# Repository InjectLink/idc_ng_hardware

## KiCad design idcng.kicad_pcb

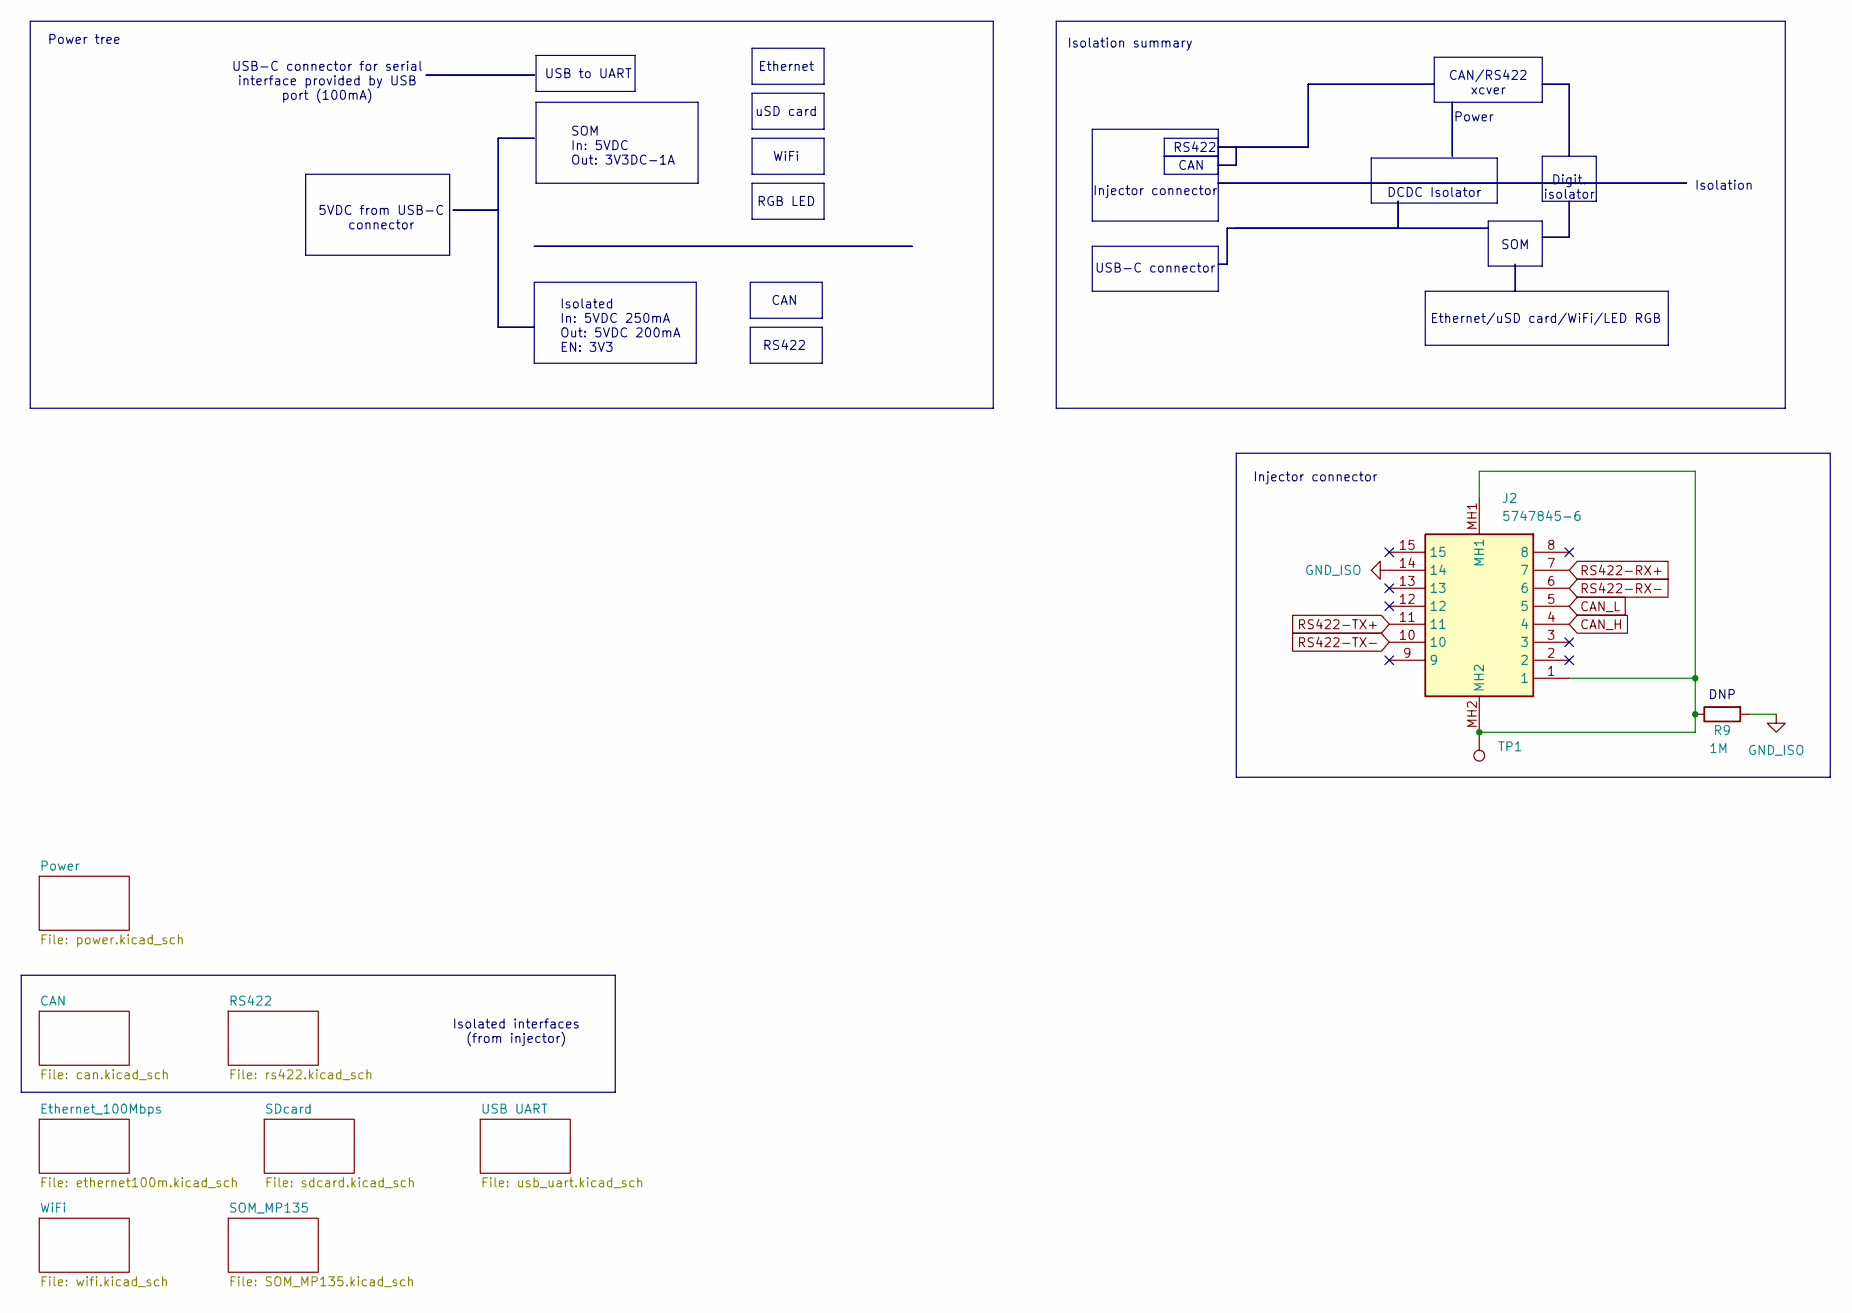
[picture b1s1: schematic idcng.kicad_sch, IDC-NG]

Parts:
J2: 5747845-6; 57478456; Mouser Part Number 571-5747845-6
R9: 1M; R_1206_3216Metric
TP1: TestPoint; TestPoint_Pad_D1.0mm

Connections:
CAN_H: J2.4; also elsewhere on the board
CAN_L: J2.5; also elsewhere on the board
GND_ISO: J2.14, R9.2; also elsewhere on the board
unnamed: J2.1, J2.MH1, J2.MH2, R9.1, TP1.1
RS422-RX+: J2.7; also elsewhere on the board
RS422-RX-: J2.6; also elsewhere on the board
RS422-TX+: J2.11; also elsewhere on the board
RS422-TX-: J2.10; also elsewhere on the board

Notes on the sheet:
SOM In: 5VDC Out: 3V3DC-1A
WiFi
DCDC Isolator
5VDC from USB-C connector
SOM
Isolated In: 5VDC 250mA Out: 5VDC 200mA EN: 3V3
Injector connector
Ethernet/uSD card/WiFi/LED RGB
Isolated interfaces (from injector)
CAN/RS422 xcver
CAN
Power
RS422
Digit. isolator
uSD card
RGB LED
USB-C connector for serial interface provided by USB port (100mA)
USB to UART
Isolation summary
USB-C connector
Ethernet
Power tree
Isolation
DNP

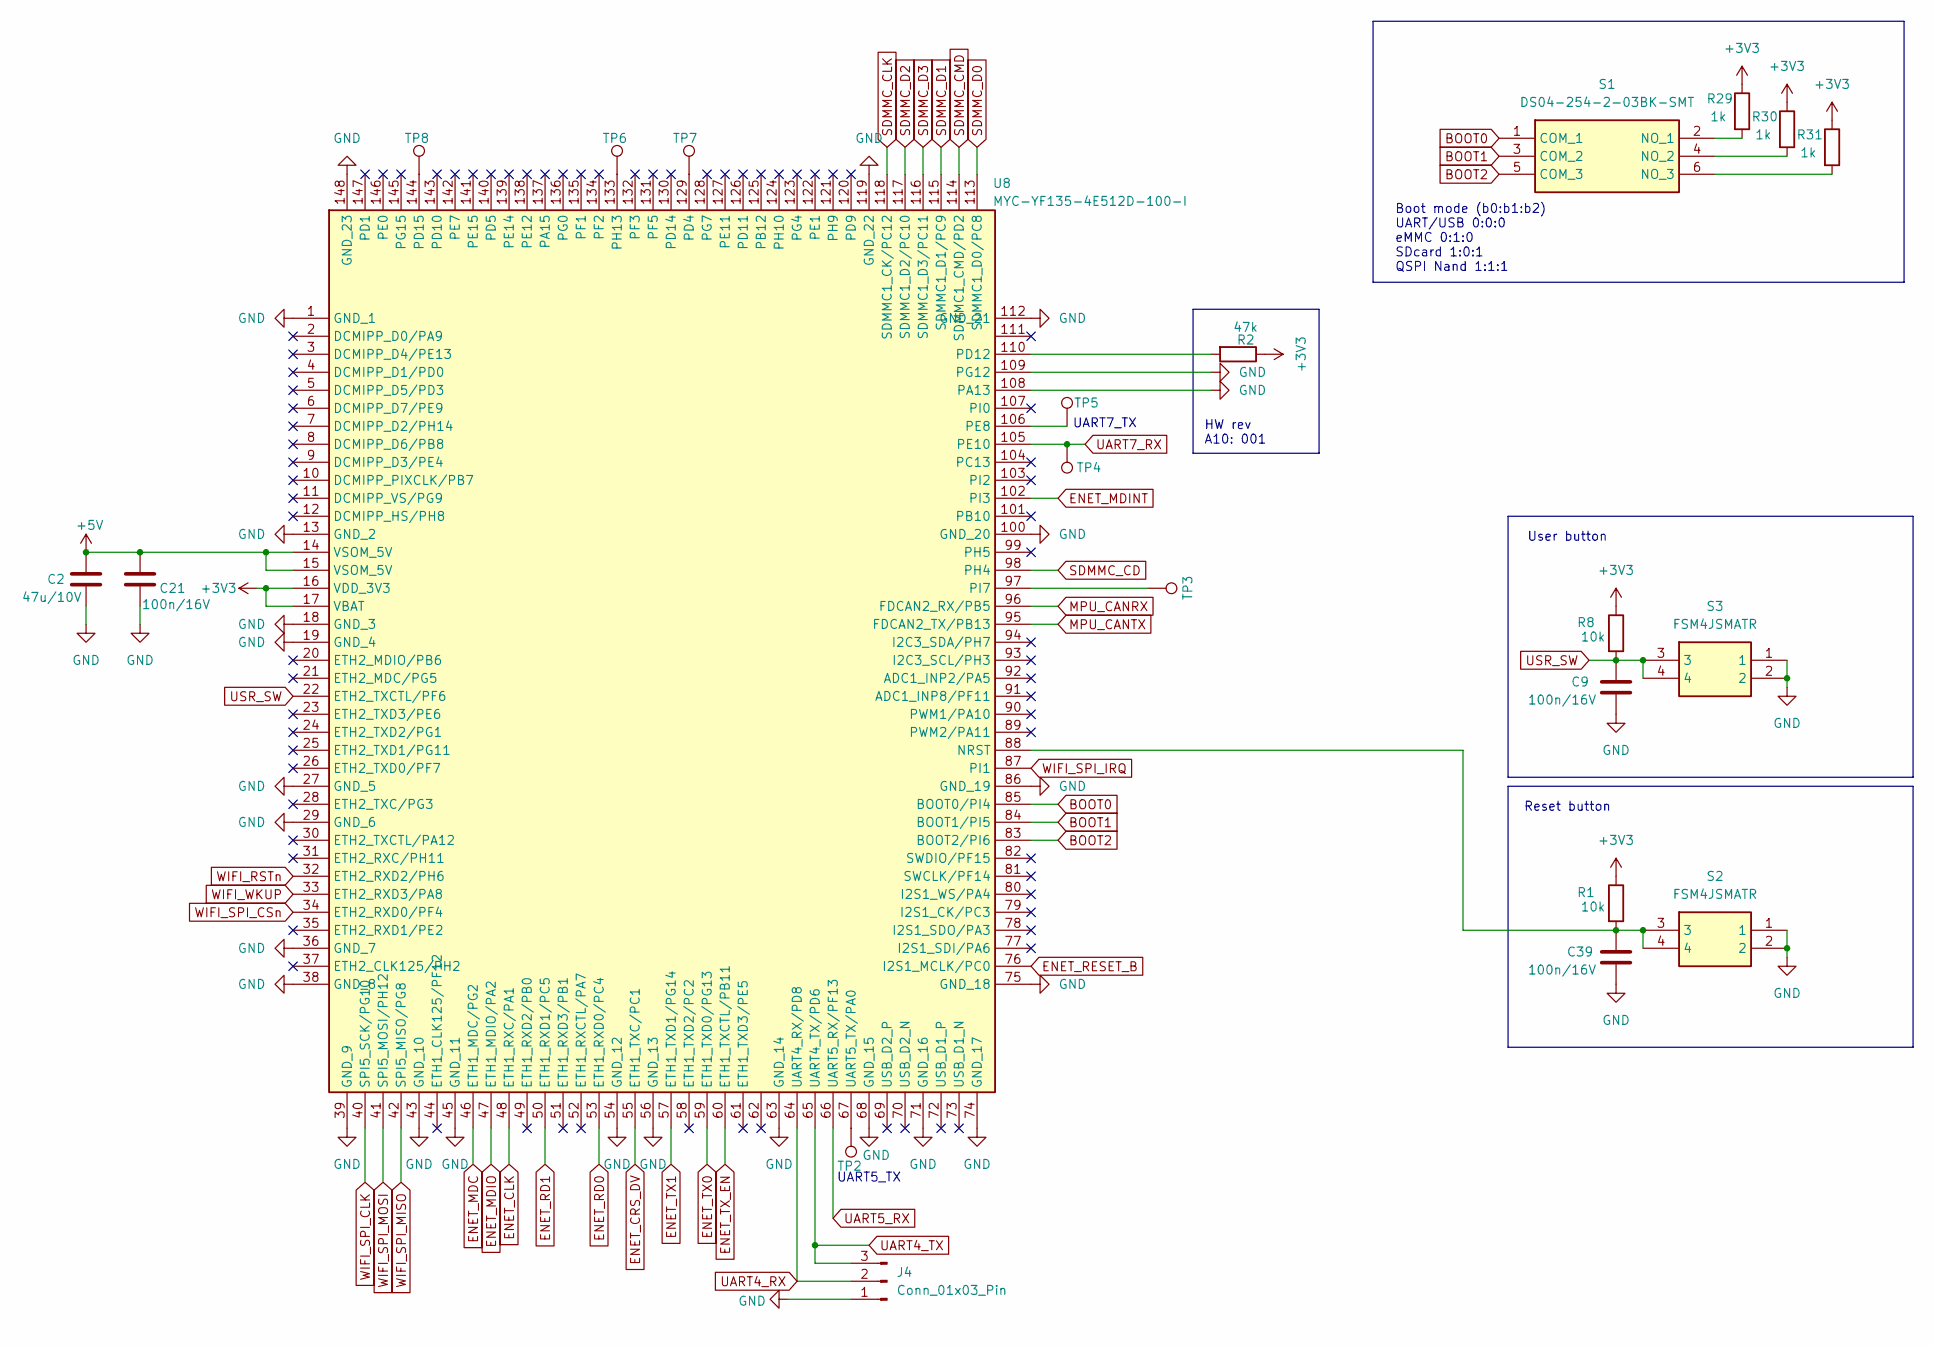
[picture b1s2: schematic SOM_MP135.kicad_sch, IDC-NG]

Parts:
C2: 47u/10V; C_1210_3225Metric
C9, C21, C39: 100n/16V; C_0201_0603Metric
J4: Conn_01x03_Pin; PinHeader_1x03_P1.00mm_Vertical
R1, R8: 10k; R_0201_0603Metric
R2: 47k; R_0201_0603Metric
R29, R30, R31: 1k; R_0201_0603Metric
S1: DS04-254-2-03BK-SMT; DS04254203BKSMT; Mouser Part Number 490-DS04254203BK-SMT
S2, S3: FSM4JSMATR; Mouser Part Number 506-FSM4JSMATR
TP2, TP3, TP4, TP5, TP6, TP7, TP8: TestPoint; TestPoint_Pad_D1.0mm
U8: MYC-YF135-4E512D-100-I; MYCYA151C256N256D65CT

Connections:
+3V3: R1.1, R2.1, R8.1, R29.1, R30.1, R31.1, U8.16 (VDD_3V3), U8.17 (VBAT); also elsewhere on the board
+5V: C2.1, C21.1, U8.14 (VSOM_5V), U8.15 (VSOM_5V); also elsewhere on the board
BOOT0: S1.1 (COM_1), U8.85 (BOOT0/PI4)
BOOT1: S1.3 (COM_2), U8.84 (BOOT1/PI5)
BOOT2: S1.5 (COM_3), U8.83 (BOOT2/PI6)
ENET_CLK: U8.48 (ETH1_RXC/PA1); also elsewhere on the board
ENET_CRS_DV: U8.55 (ETH1_TXC/PC1); also elsewhere on the board
ENET_MDC: U8.46 (ETH1_MDC/PG2); also elsewhere on the board
ENET_MDINT: U8.102 (PI3); also elsewhere on the board
ENET_MDIO: U8.47 (ETH1_MDIO/PA2); also elsewhere on the board
ENET_RD0: U8.53 (ETH1_RXD0/PC4); also elsewhere on the board
ENET_RD1: U8.50 (ETH1_RXD1/PC5); also elsewhere on the board
ENET_RESET_B: U8.76 (I2S1_MCLK/PC0); also elsewhere on the board
ENET_TX0: U8.59 (ETH1_TXD0/PG13); also elsewhere on the board
ENET_TX1: U8.57 (ETH1_TXD1/PG14); also elsewhere on the board
ENET_TX_EN: U8.60 (ETH1_TXCTL/PB11); also elsewhere on the board
GND: C2.2, C9.2, C21.2, C39.2, J4.1, S2.1, S2.2, S3.1, S3.2, U8.1 (GND_1), U8.13 (GND_2), U8.18 (GND_3), U8.19 (GND_4), U8.27 (GND_5), U8.29 (GND_6), U8.36 (GND_7), U8.38 (GND_8), U8.39 (GND_9), U8.43 (GND_10), U8.45 (GND_11), U8.54 (GND_12), U8.56 (GND_13), U8.63 (GND_14), U8.68 (GND_15), U8.71 (GND_16), U8.74 (GND_17), U8.75 (GND_18), U8.86 (GND_19), U8.100 (GND_20), U8.108 (PA13), U8.109 (PG12), U8.112 (GND_21), U8.119 (GND_22), U8.148 (GND_23); also elsewhere on the board
MPU_CANRX: U8.96 (FDCAN2_RX/PB5); also elsewhere on the board
MPU_CANTX: U8.95 (FDCAN2_TX/PB13); also elsewhere on the board
unnamed: R29.2, S1.2 (NO_1)
unnamed: R30.2, S1.4 (NO_2)
unnamed: R31.2, S1.6 (NO_3)
unnamed: C39.1, R1.2, S2.3, S2.4, U8.88 (NRST)
unnamed: TP7.1, U8.129 (PD4)
unnamed: R2.2, U8.110 (PD12)
unnamed: TP8.1, U8.144 (PD15)
unnamed: TP5.1, U8.106 (PE8)
unnamed: TP6.1, U8.133 (PH13)
unnamed: TP3.1, U8.97 (PI7)
unnamed: TP2.1, U8.67 (UART5_TX/PA0)
SDMMC_CD: U8.98 (PH4); also elsewhere on the board
SDMMC_CLK: U8.118 (SDMMC1_CK/PC12); also elsewhere on the board
SDMMC_CMD: U8.114 (SDMMC1_CMD/PD2); also elsewhere on the board
SDMMC_D0: U8.113 (SDMMC1_D0/PC8); also elsewhere on the board
SDMMC_D1: U8.115 (SDMMC1_D1/PC9); also elsewhere on the board
SDMMC_D2: U8.117 (SDMMC1_D2/PC10); also elsewhere on the board
SDMMC_D3: U8.116 (SDMMC1_D3/PC11); also elsewhere on the board
UART4_RX: J4.2, U8.64 (UART4_RX/PD8); also elsewhere on the board
UART4_TX: J4.3, U8.65 (UART4_TX/PD6); also elsewhere on the board
UART5_RX: U8.66 (UART5_RX/PF13); also elsewhere on the board
UART7_RX: TP4.1, U8.105 (PE10); also elsewhere on the board
USR_SW: C9.1, R8.2, S3.3, S3.4, U8.22 (ETH2_TXCTL/PF6)
WIFI_RSTn: U8.32 (ETH2_RXD2/PH6); also elsewhere on the board
WIFI_SPI_CLK: U8.40 (SPI5_SCK/PG10); also elsewhere on the board
WIFI_SPI_CSn: U8.34 (ETH2_RXD0/PF4); also elsewhere on the board
WIFI_SPI_IRQ: U8.87 (PI1); also elsewhere on the board
WIFI_SPI_MISO: U8.42 (SPI5_MISO/PG8); also elsewhere on the board
WIFI_SPI_MOSI: U8.41 (SPI5_MOSI/PH12); also elsewhere on the board
WIFI_WKUP: U8.33 (ETH2_RXD3/PA8); also elsewhere on the board

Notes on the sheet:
HW rev A10: 001
UART5_TX
Reset button
Boot mode (b0:b1:b2) UART/USB 0:0:0 eMMC 0:1:0 SDcard 1:0:1 QSPI Nand 1:1:1
UART7_TX
User button

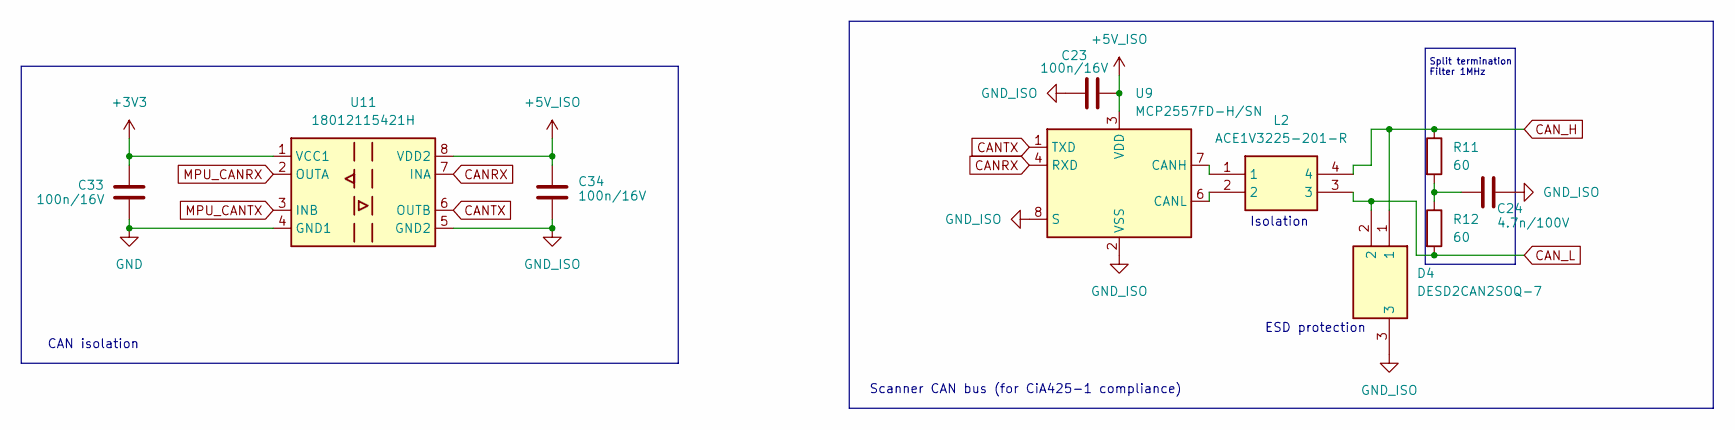
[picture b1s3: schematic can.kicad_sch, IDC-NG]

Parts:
C23, C33, C34: 100n/16V; C_0201_0603Metric
C24: 4.7n/100V; C_0603_1608Metric
D4: DESD2CAN2SOQ-7; SOT96P240X110-3N; Mouser Part Number 621-DESD2CAN2SOQ-7
L2: ACE1V3225-201-R; ACE1V3225201R; Mouser Part Number 504-ACE1V3225-201-R
R11, R12: 60; R_0201_0603Metric
U9: MCP2557FD-H/SN; SOIC-8_3.9x4.9mm_P1.27mm
U11: 18012115421H; SOIC-8_7.5x5.85mm_P1.27mm

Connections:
+3V3: C33.1, U11.1 (VCC1); also elsewhere on the board
+5V_ISO: C23.2, C34.1, U9.3 (VDD), U11.8 (VDD2); also elsewhere on the board
CANRX: U9.4 (RXD), U11.7 (INA)
CANTX: U9.1 (TXD), U11.6 (OUTB)
CAN_H: D4.1, L2.4, R11.1; also elsewhere on the board
CAN_L: D4.2, L2.3, R12.2; also elsewhere on the board
GND: C33.2, U11.4 (GND1); also elsewhere on the board
GND_ISO: C23.1, C24.1, C34.2, D4.3, U9.2 (VSS), U9.8 (S), U11.5 (GND2); also elsewhere on the board
MPU_CANRX: U11.2 (OUTA); also elsewhere on the board
MPU_CANTX: U11.3 (INB); also elsewhere on the board
unnamed: C24.2, R11.2, R12.1
unnamed: L2.1, U9.7 (CANH)
unnamed: L2.2, U9.6 (CANL)

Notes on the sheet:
ESD protection
Scanner CAN bus (for CiA425-1 compliance)
Split termination Filter 1MHz
Isolation
CAN isolation

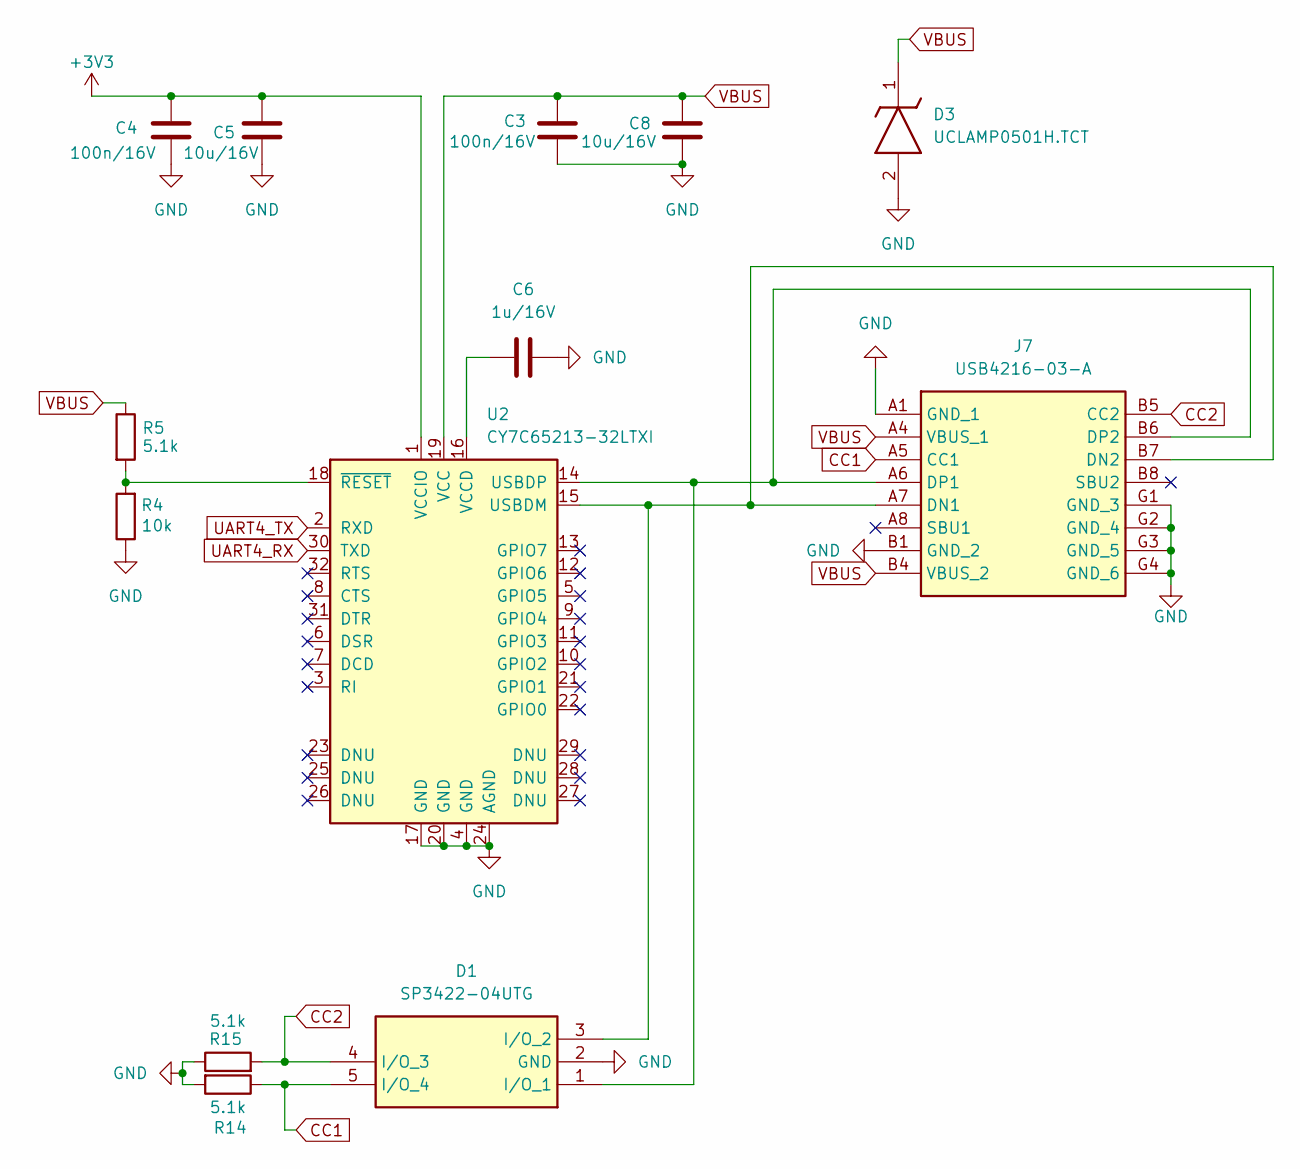
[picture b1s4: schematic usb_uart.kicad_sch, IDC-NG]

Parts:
C3, C4: 100n/16V; C_0201_0603Metric
C5, C8: 10u/16V; C_0805_2012Metric
C6: 1u/16V; C_0603_1608Metric
D1: SP3422-04UTG; SP342204UTG; Mouser Part Number 576-SP3422-04UTG
D3: UCLAMP0501H.TCT; SODFL1608X70N; Mouser Part Number 947-UCLAMP0501H.TCT
J7: USB4216-03-A; USB421603A; Mouser Part Number 640-USB4216-03-A
R4: 10k; R_0201_0603Metric
R5, R14, R15: 5.1k; R_0201_0603Metric
U2: CY7C65213-32LTXI; QFN-32-1EP_5x5mm_P0.5mm_EP3.45x3.45mm

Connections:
+3V3: C4.1, C5.1, U2.1 (VCCIO); also elsewhere on the board
CC1: D1.5 (I/O_4), J7.A5 (CC1), R14.1
CC2: D1.4 (I/O_3), J7.B5 (CC2), R15.2
GND: C3.2, C4.2, C5.2, C6.1, C8.2, D1.2 (GND), D3.2 (A), J7.A1 (GND_1), J7.B1 (GND_2), J7.G1 (GND_3), J7.G2 (GND_4), J7.G3 (GND_5), J7.G4 (GND_6), R4.1, R14.2, R15.1, U2.4 (GND), U2.17 (GND), U2.20 (GND), U2.24 (AGND); also elsewhere on the board
unnamed: D1.1 (I/O_1), J7.A6 (DP1), J7.B6 (DP2), U2.14 (USBDP)
unnamed: D1.3 (I/O_2), J7.A7 (DN1), J7.B7 (DN2), U2.15 (USBDM)
unnamed: C6.2, U2.16 (VCCD)
unnamed: R4.2, R5.2, U2.18 (~RESET)
UART4_RX: U2.30 (TXD); also elsewhere on the board
UART4_TX: U2.2 (RXD); also elsewhere on the board
VBUS: C3.1, C8.1, D3.1 (K), J7.A4 (VBUS_1), J7.B4 (VBUS_2), R5.1, U2.19 (VCC)

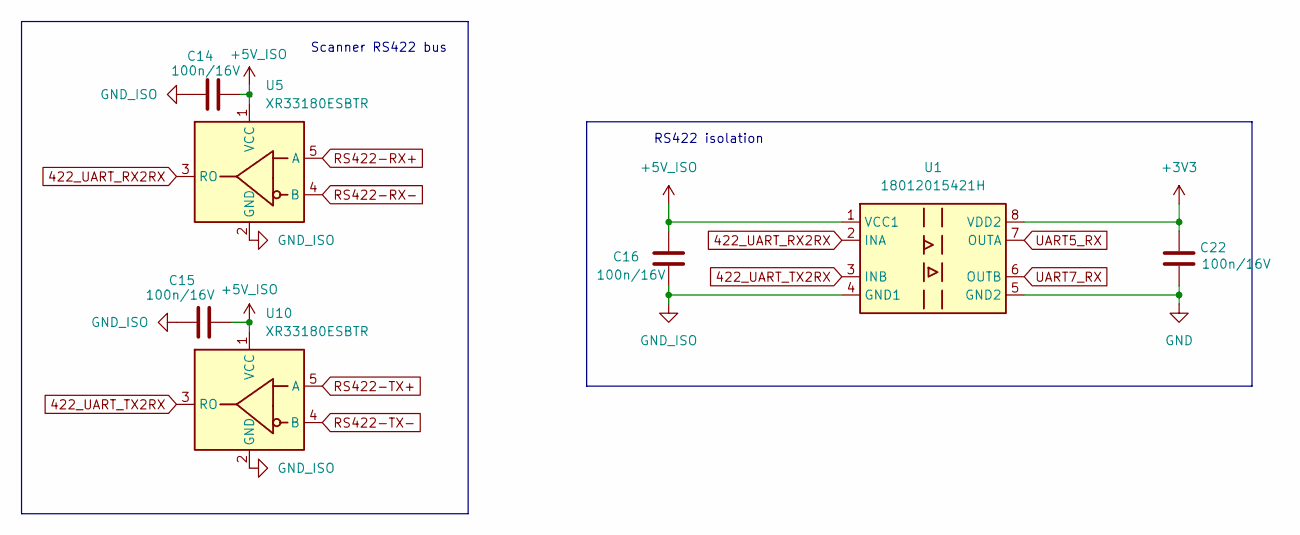
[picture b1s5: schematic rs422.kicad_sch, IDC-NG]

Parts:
C14, C15, C16, C22: 100n/16V; C_0201_0603Metric
U1: 18012015421H; SOIC-8_7.5x5.85mm_P1.27mm
U5, U10: XR33180ESBTR; TSOT-23-5

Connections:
422_UART_RX2RX: U1.2 (INA), U5.3 (RO)
422_UART_TX2RX: U1.3 (INB), U10.3 (RO)
+3V3: C22.1, U1.8 (VDD2); also elsewhere on the board
+5V_ISO: C14.1, C15.1, C16.1, U1.1 (VCC1), U5.1 (VCC), U10.1 (VCC); also elsewhere on the board
GND: C22.2, U1.5 (GND2); also elsewhere on the board
GND_ISO: C14.2, C15.2, C16.2, U1.4 (GND1), U5.2 (GND), U10.2 (GND); also elsewhere on the board
RS422-RX+: U5.5 (A); also elsewhere on the board
RS422-RX-: U5.4 (B); also elsewhere on the board
RS422-TX+: U10.5 (A); also elsewhere on the board
RS422-TX-: U10.4 (B); also elsewhere on the board
UART5_RX: U1.7 (OUTA); also elsewhere on the board
UART7_RX: U1.6 (OUTB); also elsewhere on the board

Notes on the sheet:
RS422 isolation
Scanner RS422 bus

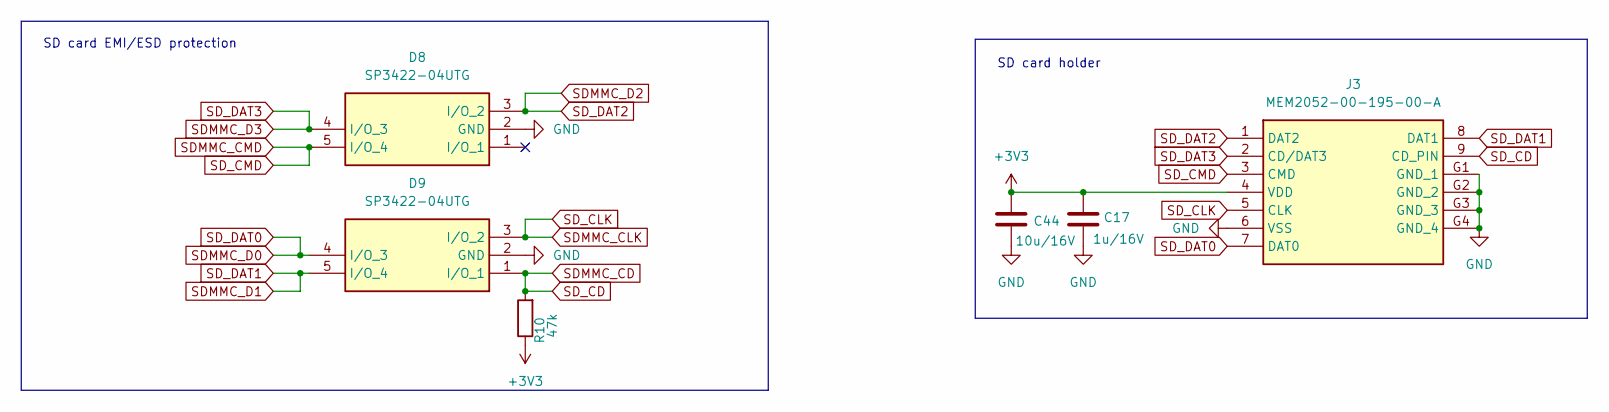
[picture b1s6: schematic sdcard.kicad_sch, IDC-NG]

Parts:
C17: 1u/16V; C_0603_1608Metric
C44: 10u/16V; C_0805_2012Metric
D8, D9: SP3422-04UTG; SP342204UTG; Mouser Part Number 576-SP3422-04UTG
J3: MEM2052-00-195-00-A; MEM20520019500A; Mouser Part Number 640-MEM20520019500A
R10: 47k; R_0201_0603Metric

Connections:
+3V3: C17.1, C44.1, J3.4 (VDD), R10.1; also elsewhere on the board
GND: C17.2, C44.2, D8.2 (GND), D9.2 (GND), J3.6 (VSS), J3.G1 (GND_1), J3.G2 (GND_2), J3.G3 (GND_3), J3.G4 (GND_4); also elsewhere on the board
SDMMC_CD: D9.1 (I/O_1), J3.9 (CD_PIN), R10.2; also elsewhere on the board
SDMMC_CLK: D9.3 (I/O_2), J3.5 (CLK); also elsewhere on the board
SDMMC_CMD: D8.5 (I/O_4), J3.3 (CMD); also elsewhere on the board
SDMMC_D0: D9.4 (I/O_3), J3.7 (DAT0); also elsewhere on the board
SDMMC_D1: D9.5 (I/O_4), J3.8 (DAT1); also elsewhere on the board
SDMMC_D2: D8.3 (I/O_2), J3.1 (DAT2); also elsewhere on the board
SDMMC_D3: D8.4 (I/O_3), J3.2 (CD/DAT3); also elsewhere on the board

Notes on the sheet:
SD card EMI/ESD protection
SD card holder

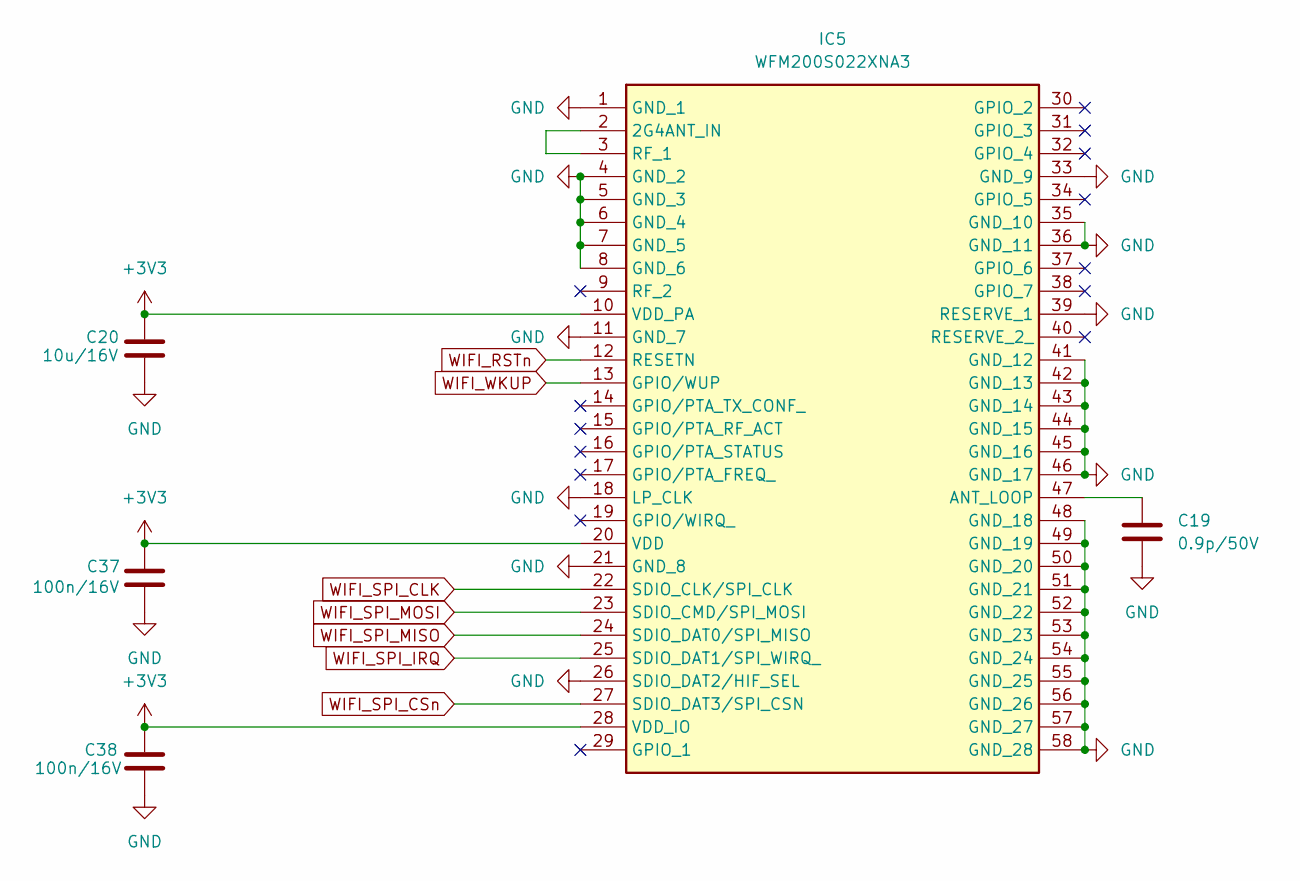
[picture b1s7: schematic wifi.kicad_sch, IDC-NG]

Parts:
C19: 0.9p/50V; C_0201_0603Metric
C20: 10u/16V; C_0805_2012Metric
C37, C38: 100n/16V; C_0201_0603Metric
IC5: WFM200S022XNA3; Mouser Part Number 634-WFM200S022XNA3

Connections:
+3V3: C20.1, C37.1, C38.1, IC5.10 (VDD_PA), IC5.20 (VDD), IC5.28 (VDD_IO); also elsewhere on the board
GND: C19.2, C20.2, C37.2, C38.2, IC5.1 (GND_1), IC5.4 (GND_2), IC5.5 (GND_3), IC5.6 (GND_4), IC5.7 (GND_5), IC5.8 (GND_6), IC5.11 (GND_7), IC5.18 (LP_CLK), IC5.21 (GND_8), IC5.26 (SDIO_DAT2/HIF_SEL), IC5.33 (GND_9), IC5.35 (GND_10), IC5.36 (GND_11), IC5.39 (RESERVE_1), IC5.41 (GND_12), IC5.42 (GND_13), IC5.43 (GND_14), IC5.44 (GND_15), IC5.45 (GND_16), IC5.46 (GND_17), IC5.48 (GND_18), IC5.49 (GND_19), IC5.50 (GND_20), IC5.51 (GND_21), IC5.52 (GND_22), IC5.53 (GND_23), IC5.54 (GND_24), IC5.55 (GND_25), IC5.56 (GND_26), IC5.57 (GND_27), IC5.58 (GND_28); also elsewhere on the board
unnamed: IC5.2 (2G4ANT_IN), IC5.3 (RF_1)
unnamed: C19.1, IC5.47 (ANT_LOOP)
WIFI_RSTn: IC5.12 (RESETN); also elsewhere on the board
WIFI_SPI_CLK: IC5.22 (SDIO_CLK/SPI_CLK); also elsewhere on the board
WIFI_SPI_CSn: IC5.27 (SDIO_DAT3/SPI_CSN); also elsewhere on the board
WIFI_SPI_IRQ: IC5.25 (SDIO_DAT1/SPI_WIRQ_); also elsewhere on the board
WIFI_SPI_MISO: IC5.24 (SDIO_DAT0/SPI_MISO); also elsewhere on the board
WIFI_SPI_MOSI: IC5.23 (SDIO_CMD/SPI_MOSI); also elsewhere on the board
WIFI_WKUP: IC5.13 (GPIO/WUP); also elsewhere on the board

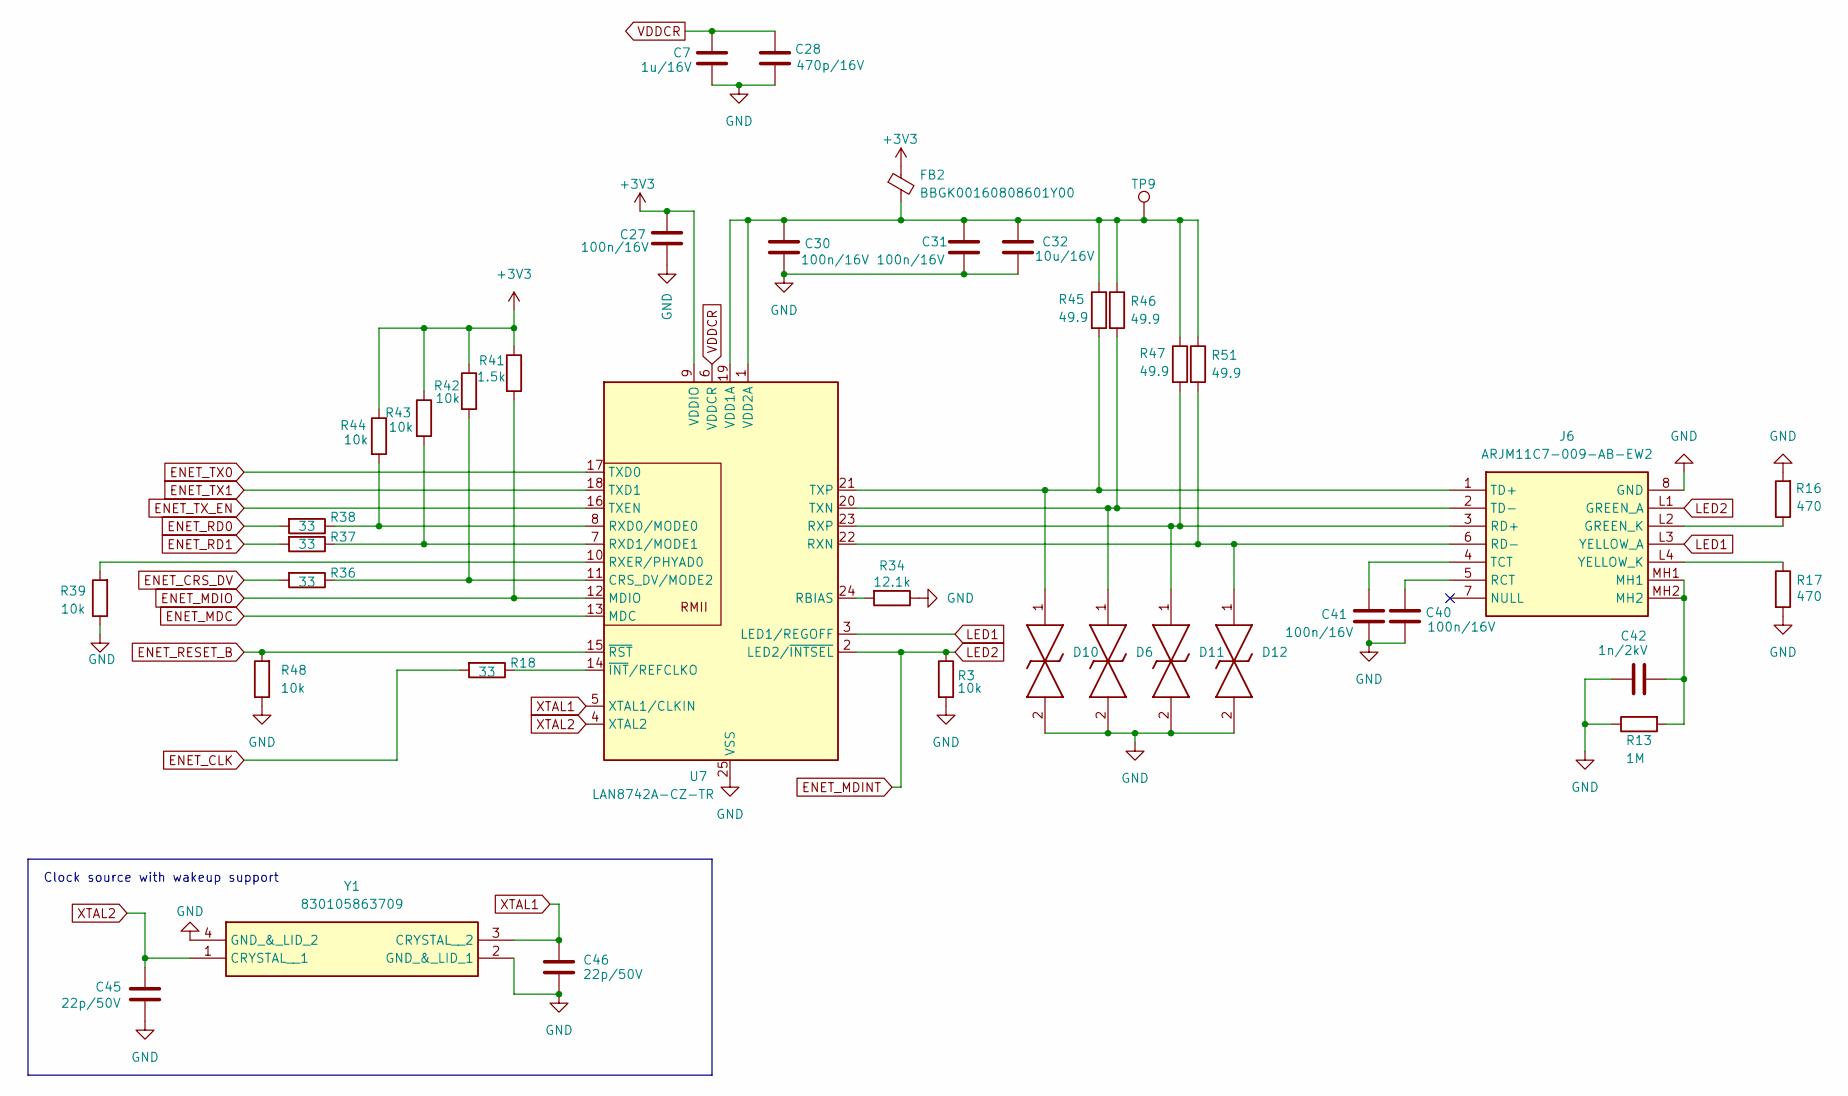
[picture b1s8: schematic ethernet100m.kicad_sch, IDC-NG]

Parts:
C7: 1u/16V; C_0603_1608Metric
C27, C30, C31, C40, C41: 100n/16V; C_0201_0603Metric
C28: 470p/16V; C_0402_1005Metric
C32: 10u/16V; C_0805_2012Metric
C42: 1n/2kV; C_1206_3216Metric
C45, C46: 22p/50V; C_0201_0603Metric
D6, D10, D11, D12: AQ3130-01ETG; AQ313001ETG; Mouser Part Number 576-AQ3130-01ETG
FB2: BBGK00160808601Y00; L_0603_1608Metric
J6: ARJM11C7-009-AB-EW2; ARJM11C7009ABEW2; Mouser Part Number 815-RJM11C7009ABEW2
R3, R39, R42, R43, R44, R48: 10k; R_0201_0603Metric
R13: 1M; R_1206_3216Metric
R16, R17: 470; L_0402_1005Metric
R18, R36, R37, R38: 33; R_0201_0603Metric
R34: 12.1k; R_0201_0603Metric
R41: 1.5k; R_0402_1005Metric; Part AC0402FR-7W1K5L
R45, R46, R47, R51: 49.9; R_0201_0603Metric
TP9: TestPoint; TestPoint_Pad_D1.0mm
U7: LAN8742A-CZ-TR; VQFN-24-1EP_4x4mm_P0.5mm_EP2.5x2.5mm_ThermalVias
Y1: 830105863709; Mouser Part Number 710-830105863709

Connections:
+3V3: C27.1, FB2.1, R41.1, R42.1, R43.1, R44.1, U7.9 (VDDIO); also elsewhere on the board
ENET_CLK: R18.2; also elsewhere on the board
ENET_CRS_DV: R36.2; also elsewhere on the board
ENET_MDC: U7.13 (MDC); also elsewhere on the board
ENET_MDINT: J6.L1 (GREEN_A), R3.1, U7.2 (LED2/~INTSEL); also elsewhere on the board
ENET_MDIO: R41.2, U7.12 (MDIO); also elsewhere on the board
ENET_RD0: R38.2; also elsewhere on the board
ENET_RD1: R37.2; also elsewhere on the board
ENET_RESET_B: R48.2, U7.15 (~RST); also elsewhere on the board
ENET_TX0: U7.17 (TXD0); also elsewhere on the board
ENET_TX1: U7.18 (TXD1); also elsewhere on the board
ENET_TX_EN: U7.16 (TXEN); also elsewhere on the board
GND: C7.2, C27.2, C28.2, C30.1, C31.1, C32.1, C40.1, C41.1, C42.1, C45.2, C46.2, D6.2, D10.2, D11.2, D12.2, J6.8 (GND), R3.2, R13.1, R16.2, R17.2, R34.1, R39.1, R48.1, U7.25 (VSS), Y1.2 (GND_&_LID_1), Y1.4 (GND_&_LID_2); also elsewhere on the board
LED1: J6.L3 (YELLOW_A), U7.3 (LED1/REGOFF)
unnamed: C42.2, J6.MH1, J6.MH2, R13.2
unnamed: J6.L2 (GREEN_K), R16.1
unnamed: C40.2, J6.5 (RCT)
unnamed: D11.1, J6.3 (RD+), R47.2, U7.23 (RXP)
unnamed: D12.1, J6.6 (RD-), R51.2, U7.22 (RXN)
unnamed: C41.2, J6.4 (TCT)
unnamed: D10.1, J6.1 (TD+), R45.2, U7.21 (TXP)
unnamed: D6.1, J6.2 (TD-), R46.2, U7.20 (TXN)
unnamed: J6.L4 (YELLOW_K), R17.1
unnamed: R36.1, R42.2, U7.11 (CRS_DV/MODE2)
unnamed: R34.2, U7.24 (RBIAS)
unnamed: R38.1, R44.2, U7.8 (RXD0/MODE0)
unnamed: R37.1, R43.2, U7.7 (RXD1/MODE1)
unnamed: R39.2, U7.10 (RXER/PHYAD0)
unnamed: C30.2, C31.2, C32.2, FB2.2, R45.1, R46.1, R47.1, R51.1, TP9.1, U7.1 (VDD2A), U7.19 (VDD1A)
unnamed 59: R18.1, U7.14 (~INT/REFCLKO); also elsewhere on the board
VDDCR: C7.1, C28.1, U7.6 (VDDCR)
XTAL1: C46.1, U7.5 (XTAL1/CLKIN), Y1.3 (CRYSTAL__2)
XTAL2: C45.1, U7.4 (XTAL2), Y1.1 (CRYSTAL__1)

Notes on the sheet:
Clock source with wakeup support

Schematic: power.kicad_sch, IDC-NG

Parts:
C1, C35: 100n/16V; C_0201_0603Metric
C10: 1nF/300VAC; VY2102M29Y5US6TV7; Mouser Part Number 72-VY2102M29Y5US6TV7
C36: 10u/16V; C_0805_2012Metric
C43: 22u/16V; C_0603_1608Metric
D2: UCLAMP0501H.TCT; SODFL1608X70N; Mouser Part Number 947-UCLAMP0501H.TCT
D7: SP3422-04UTG; SP342204UTG; Mouser Part Number 576-SP3422-04UTG
F1: SF-0603F250-2; Fuse_0603_1608Metric
IC1: MIE1W0505BGLVH-3R-P; MIE1W0505BGLVH3RP; Mouser Part Number 946-MIE1W0505BGLVH3P
J1: USB4216-03-A; USB421603A; Mouser Part Number 640-USB4216-03-A
R6, R7: 5.1k; R_0201_0603Metric

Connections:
+3V3: IC1.8 (EN); also elsewhere on the board
+5V: C1.1, C36.1, D2.1 (K), F1.1, IC1.9 (VIN_1), IC1.10 (VIN_2), IC1.14 (VIN_3); also elsewhere on the board
+5V_ISO: C35.1, C43.1, IC1.5 (VOUT_1), IC1.6 (VOUT_2), IC1.7 (VSEL), IC1.15 (VOUT_3); also elsewhere on the board
ESD_CC1: D7.4 (I/O_3), J1.A5 (CC1), R6.1
ESD_CC2: D7.5 (I/O_4), J1.B5 (CC2), R7.2
GND: C1.2, C10.1, C36.2, D2.2 (A), D7.2 (GND), IC1.1 (GND1_1), IC1.11 (GND1_2), IC1.12 (GND1_3), IC1.13 (GND1_4), J1.A1 (GND_1), J1.B1 (GND_2), J1.G1 (GND_3), J1.G2 (GND_4), J1.G3 (GND_5), J1.G4 (GND_6), R6.2, R7.1; also elsewhere on the board
GND_ISO: C10.2, C35.2, C43.2, IC1.2 (GND2_1), IC1.3 (GND2_2), IC1.4 (GND2_3), IC1.16 (GND2_4); also elsewhere on the board
unnamed: F1.2, J1.A4 (VBUS_1), J1.B4 (VBUS_2)

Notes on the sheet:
DNP
DCDC 5V-5V isolation (2.5kV) Efficiency 50%
Input: optional USB-C 5VDC
